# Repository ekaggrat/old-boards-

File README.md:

I collected an curated most of the common 3d printer controller boards made between 2011 and 2019. A lot of them have completely disappeared from the internet. This is just to have a library of the old board for reference.

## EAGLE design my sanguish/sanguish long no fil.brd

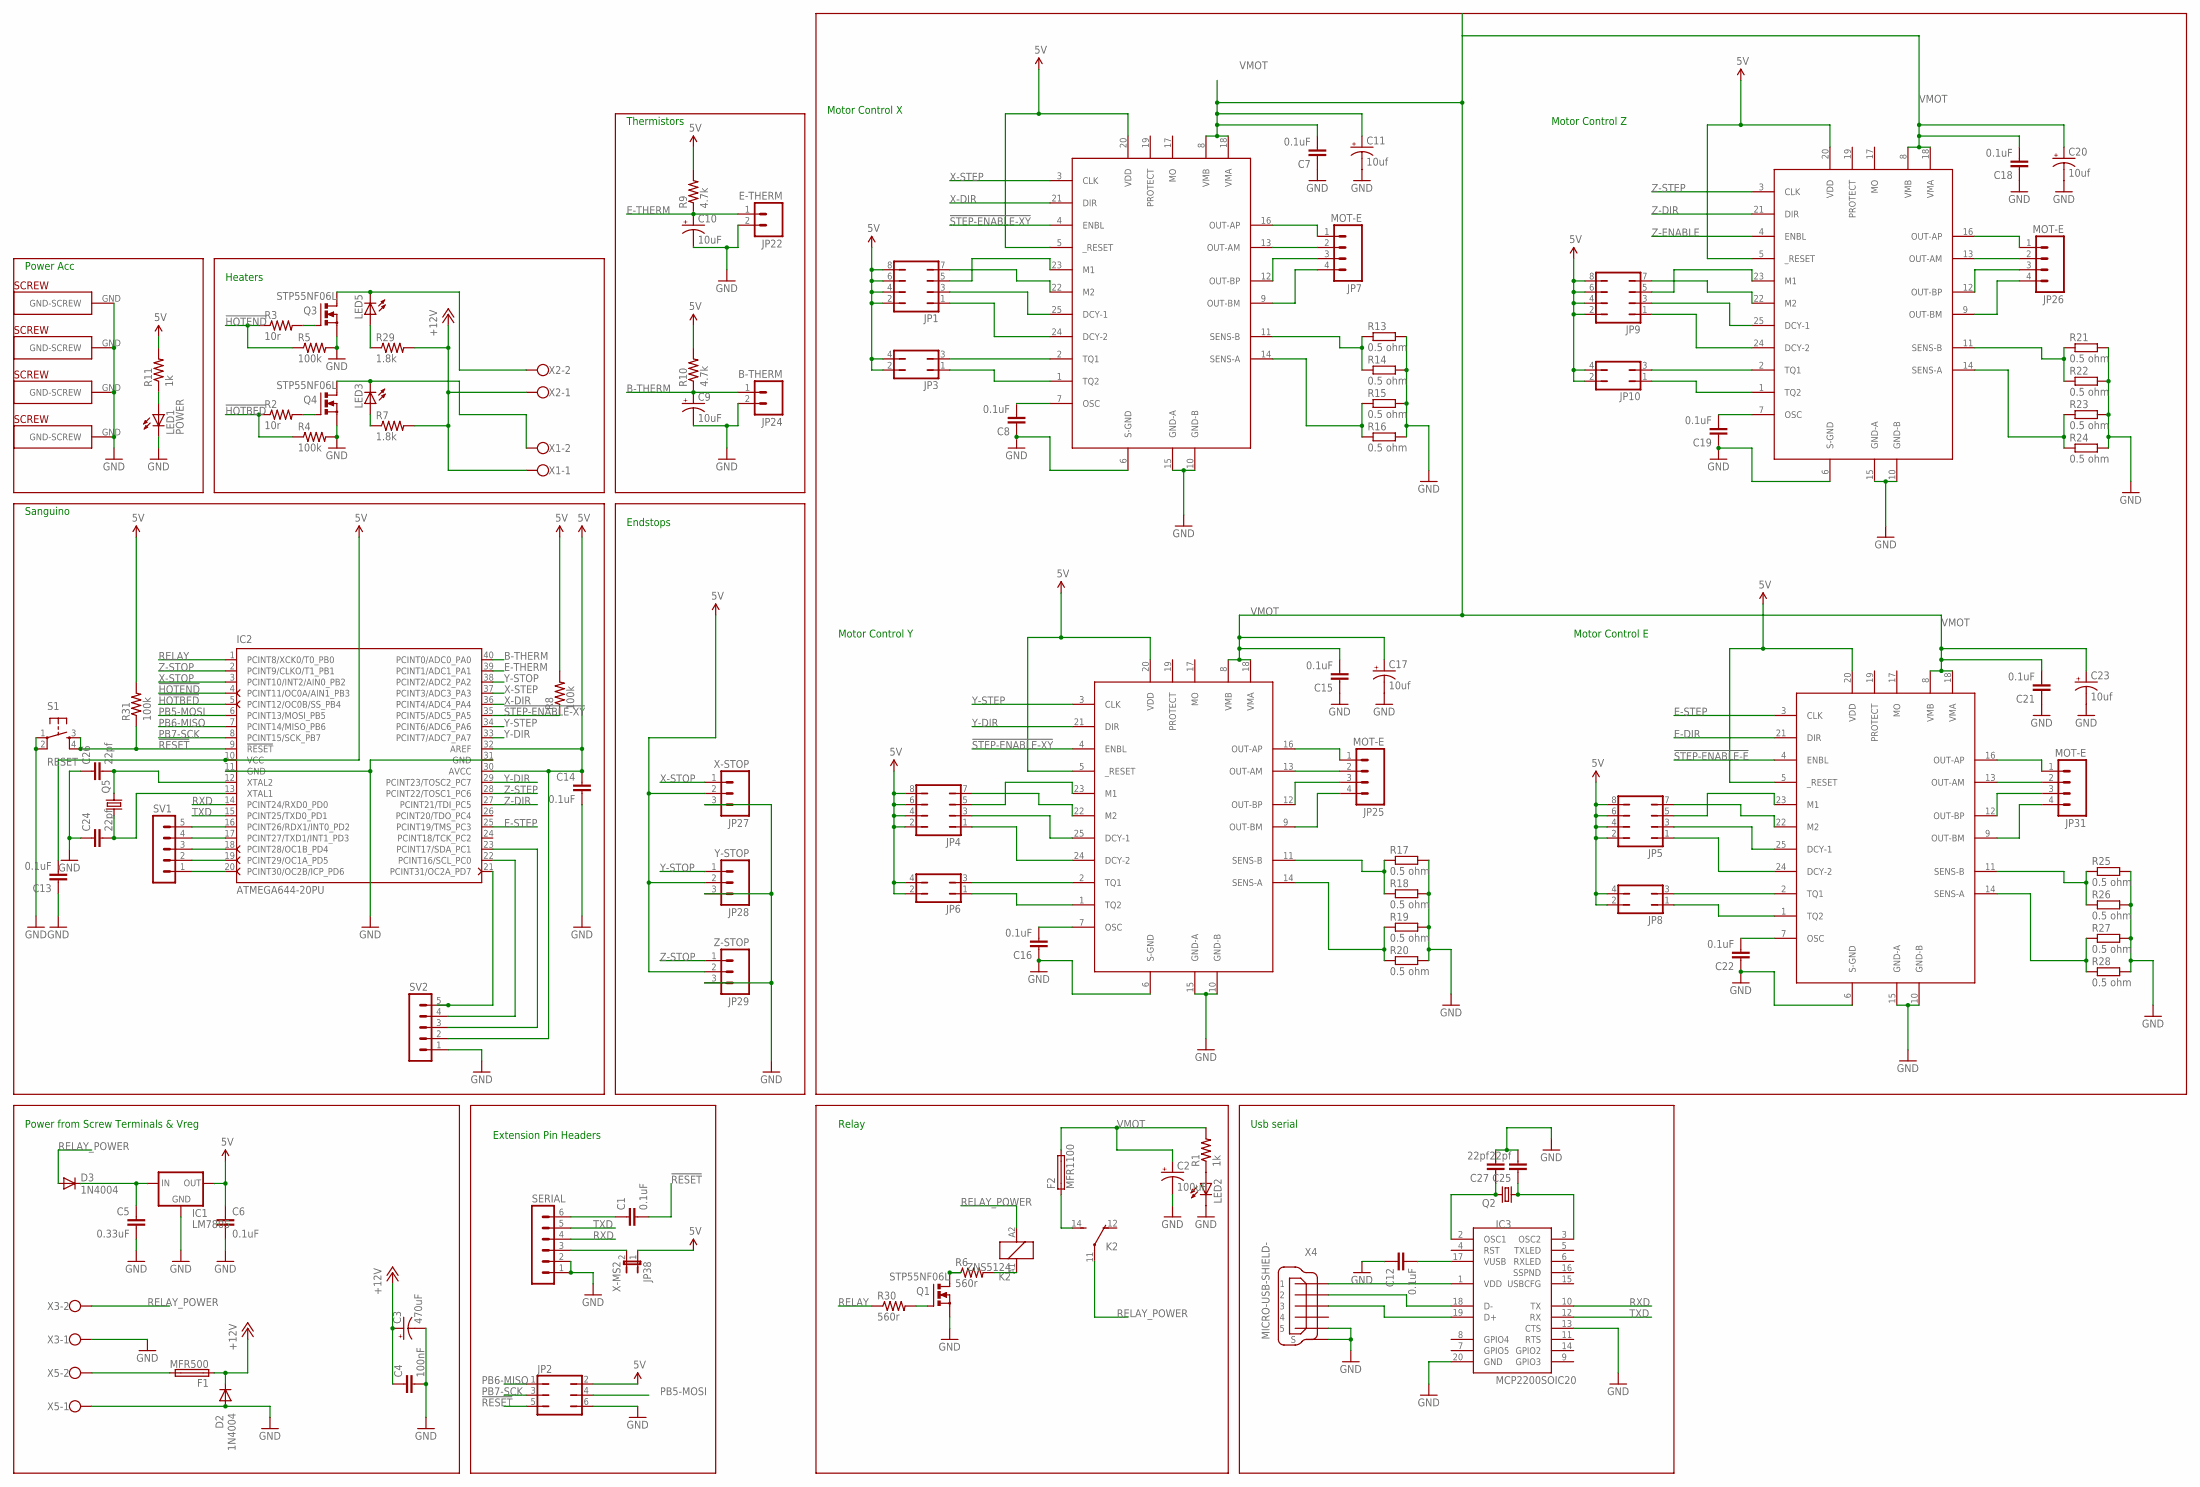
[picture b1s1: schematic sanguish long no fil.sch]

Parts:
C1, C6, C7, C8, C12, C13, C14, C15, C16, C18, C19, C21, C22: 0.1uF; CAP-PTH-SMALL2
C2: 100uF; CPOL-RADIAL-10UF-25V
C3: 470uF; E3,5-8
C4: 100nF; C2.5-3
C5: 0.33uF; CAP-PTH-SMALL2
C9, C10: 10uF; CPOL-RADIAL-10UF-25V
C11, C17, C20, C23: 10uf; CPOL-RADIAL-100UF-25V
C24, C25, C26, C27: 22pf; CAP-PTH-SMALL2
D2, D3: 1N4004; DO41-10
F1: MFR500
F2: MFR1100
IC1: LM7805; 78XXL-CUSTOM
IC2: ATMEGA644-20PU; DIL40
IC3: MCP2200SOIC20; SOIC20
JP1, JP4, JP5, JP9: JP4Q
JP2: JP3Q
JP3, JP6, JP8, JP10: JP2Q
JP7, JP25, JP26, JP31: MOT-E; MOLEX-1X4
JP22: E-THERM; 1X02
JP24: B-THERM; 1X02
JP27: X-STOP; MOLEX-1X3
JP28: Y-STOP; MOLEX-1X3
JP29: Z-STOP; MOLEX-1X3
JP38: X-MS2; 1X02
K2: ZNS5124; ZN5
LED1: POWER; LED3MM
LED2, LED3, LED5: LED3MM
Q1, Q3, Q4: STP55NF06L; TO220BV
Q2, Q5: CRYSTALHC49S; HC49/S
R1, R11: 1k; 0207/2V
R2, R3: 10r; 0207/2V
R4, R5, R8, R31: 100k; 0207/2V
R6, R30: 560r; 0207/2V
R7, R29: 1.8k; 0207/2V
R9, R10: 4.7k; 0207/2V
R13, R14, R15, R16, R17, R18, R19, R20, R21, R22, R23, R24, R25, R26, R27, R28: 0.5 ohm; 0207/10
S1: RESET; TACTILE-PTH
SERIAL: MA06-1
SV1, SV2: MA05-1
U$7, U$17, U$37, U$38: PLATED-SCREW; PLATEDSCREW
U$21, U$43, U$46: TB6560; ZIP25
X1, X3, X5: W237-102; MPN 237-102
X2: W237-102
X4: MICRO-USB-SHIELD-; 10118192-0001LF
XMOT: TB6560; ZIP25

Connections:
5V: C6.1, C13.2, C14.1, IC1.OUT, IC2.10 (VCC), IC2.30 (AVCC), IC2.32 (AREF), JP1.2, JP1.4, JP1.6, JP1.8, JP2.2, JP3.2, JP3.4, JP4.2, JP4.4, JP4.6, JP4.8, JP5.2, JP5.4, JP5.6, JP5.8, JP6.2, JP6.4, JP8.2, JP8.4, JP9.2, JP9.4, JP9.6, JP9.8, JP10.2, JP10.4, JP27.2, JP28.2, JP29.2, JP38.1, R8.2, R9.2, R10.2, R11.2, R31.2, SV2.2, U$21.5 (_RESET), U$21.20 (VDD), U$43.5 (_RESET), U$43.20 (VDD), U$46.5 (_RESET), U$46.20 (VDD), XMOT.5 (_RESET), XMOT.20 (VDD)
!HOTBED: IC2.5 (PCINT12/OC0B/SS_PB4), R2.1, R4.1
!HOTEND: IC2.4 (PCINT11/OC0A/AIN1_PB3), R3.1, R5.1
!RESET: C1.2, IC2.9 (!RESET), JP2.5, R31.1, S1.3, S1.4
!STEP-ENABLE-E: U$46.4 (ENBL)
!STEP-ENABLE-XY: IC2.35 (PCINT5/ADC5_PA5), R8.1, U$21.4 (ENBL), XMOT.4 (ENBL)
+12V: C3.+, C4.1, D2.C, F1.1, R7.2, R29.2, X1.1, X2.1
B-THERM: C9.1 (+), IC2.40 (PCINT0/ADC0_PA0), JP24.1, R10.1
E-DIR: U$46.21 (DIR)
E-STEP: IC2.25 (PCINT19/TMS_PC3), U$46.3 (CLK)
E-THERM: C10.1 (+), IC2.39 (PCINT1/ADC1_PA1), JP22.1, R9.1
GND: C2.2 (-), C3.-, C4.2, C5.2, C6.2, C7.1, C8.1, C9.2 (-), C10.2 (-), C11.2 (-), C12.1, C13.1, C14.2, C15.1, C16.1, C17.2 (-), C18.1, C19.1, C20.2 (-), C21.1, C22.1, C23.2 (-), C24.1, C25.2, C26.1, C27.2, D2.A, IC1.GND, IC2.11 (GND), IC2.31 (GND), IC3.13 (CTS), IC3.20 (GND), JP2.6, JP22.2, JP24.2, JP27.3, JP28.3, JP29.3, LED1.K (C), LED2.K (C), Q1.S, Q3.S, Q4.S, R4.2, R5.2, R13.2, R14.2, R15.2, R16.2, R17.2, R18.2, R19.2, R20.2, R21.2, R22.2, R23.2, R24.2, R25.2, R26.2, R27.2, R28.2, S1.1, S1.2, SERIAL.1, SERIAL.2, SV2.1, U$7.GND, U$17.GND, U$21.6 (S-GND), U$21.10 (GND-B), U$21.15 (GND-A), U$37.GND, U$38.GND, U$43.6 (S-GND), U$43.10 (GND-B), U$43.15 (GND-A), U$46.6 (S-GND), U$46.10 (GND-B), U$46.15 (GND-A), X3.1, X4.5, X4.M1 (S), X4.M2 (S), X4.M3 (S), X4.M4 (S), X4.M5 (S), X4.M6 (S), X5.1, XMOT.6 (S-GND), XMOT.10 (GND-B), XMOT.15 (GND-A)
LED1: LED1.A, R11.1
unnamed: JP7.1, XMOT.16 (OUT-AP)
unnamed: JP25.1, U$21.16 (OUT-AP)
unnamed: JP7.2, XMOT.13 (OUT-AM)
unnamed: JP7.3, XMOT.12 (OUT-BP)
unnamed: JP7.4, XMOT.9 (OUT-BM)
unnamed: JP5.7, U$46.22 (M2)
unnamed: JP1.7, XMOT.22 (M2)
unnamed: JP1.3, XMOT.25 (DCY-1)
unnamed: JP1.1, XMOT.24 (DCY-2)
unnamed: JP10.3, U$43.2 (TQ1)
unnamed: JP3.1, XMOT.1 (TQ2)
unnamed: JP5.5, U$46.23 (M1)
unnamed: JP25.2, U$21.13 (OUT-AM)
unnamed: JP25.3, U$21.12 (OUT-BP)
unnamed: R13.1, R14.1, XMOT.11 (SENS-B)
unnamed: R15.1, R16.1, XMOT.14 (SENS-A)
unnamed: JP25.4, U$21.9 (OUT-BM)
unnamed: JP9.7, U$43.22 (M2)
unnamed: C8.2, XMOT.7 (OSC)
unnamed: JP4.7, U$21.22 (M2)
unnamed: JP4.3, U$21.25 (DCY-1)
unnamed: JP4.1, U$21.24 (DCY-2)
unnamed: JP9.5, U$43.23 (M1)
unnamed: JP8.3, U$46.2 (TQ1)
unnamed: JP5.3, U$46.25 (DCY-1)
unnamed: R17.1, R18.1, U$21.11 (SENS-B)
unnamed: R19.1, R20.1, U$21.14 (SENS-A)
unnamed: C16.2, U$21.7 (OSC)
unnamed: JP26.1, U$43.16 (OUT-AP)
unnamed: JP26.2, U$43.13 (OUT-AM)
unnamed: JP26.3, U$43.12 (OUT-BP)
unnamed: JP26.4, U$43.9 (OUT-BM)
unnamed: JP5.1, U$46.24 (DCY-2)
unnamed: JP6.3, U$21.2 (TQ1)
unnamed: JP8.1, U$46.1 (TQ2)
unnamed: JP3.3, XMOT.2 (TQ1)
unnamed: JP4.5, U$21.23 (M1)
unnamed: JP1.5, XMOT.23 (M1)
unnamed: JP9.3, U$43.25 (DCY-1)
unnamed: R21.1, R22.1, U$43.11 (SENS-B)
unnamed: R23.1, R24.1, U$43.14 (SENS-A)
unnamed: C19.2, U$43.7 (OSC)
unnamed: JP31.1, U$46.16 (OUT-AP)
unnamed: JP31.2, U$46.13 (OUT-AM)
unnamed: JP31.3, U$46.12 (OUT-BP)
unnamed: JP31.4, U$46.9 (OUT-BM)
unnamed: LED2.A, R1.1
unnamed: IC2.16 (PCINT26/RDX1/INT0_PD2), SV1.5
unnamed: IC2.17 (PCINT27/TXD1/INT1_PD3), SV1.4
unnamed: IC2.18 (PCINT28/OC1B_PD4), SV1.3
unnamed: IC2.19 (PCINT29/OC1A_PD5), SV1.2
unnamed: R25.1, R26.1, U$46.11 (SENS-B)
unnamed: R27.1, R28.1, U$46.14 (SENS-A)
unnamed: C22.2, U$46.7 (OSC)
unnamed: LED3.K (C), Q4.D, X1.2
unnamed: IC2.20 (PCINT30/OC2B/ICP_PD6), SV1.1
unnamed: LED5.K (C), Q3.D, X2.2
unnamed: Q4.G, R2.2
unnamed: Q3.G, R3.2
unnamed: IC2.21 (PCINT31/OC2A_PD7), SV2.5
unnamed: IC2.22 (PCINT16/SCL_PC0), SV2.4
unnamed: LED3.A, R7.1
unnamed: LED5.A, R29.1
unnamed: Q1.D, R6.1
unnamed: Q1.G, R30.2
unnamed: C5.1, D3.C, IC1.IN
unnamed: IC2.23 (PCINT17/SDA_PC1), SV2.3
unnamed: C1.1, SERIAL.6
unnamed: JP38.2, SERIAL.3
unnamed: F2.1, K2.14 (S)
unnamed: K2.A1 (1), R6.2
unnamed: F1.2, X5.2
unnamed: C12.2, IC3.17 (VUSB)
unnamed: JP6.1, U$21.1 (TQ2)
unnamed: IC3.1 (VDD), X4.1
unnamed: IC3.18 (D-), X4.2
unnamed: IC3.19 (D+), X4.3
unnamed: C26.2, IC2.12 (XTAL2), Q5.2
unnamed: C24.2, IC2.13 (XTAL1), Q5.1
unnamed: C27.1, IC3.2 (OSC1), Q2.2
unnamed: C25.1, IC3.3 (OSC2), Q2.1
PB5-MOSI: IC2.6 (PCINT13/MOSI_PB5), JP2.4
PB6-MISO: IC2.7 (PCINT14/MISO_PB6), JP2.1
PB7-SCK: IC2.8 (PCINT15/SCK_PB7), JP2.3
RELAY: IC2.1 (PCINT8/XCK0/T0_PB0), R30.1
RELAY_POWER: D3.A, K2.11, K2.A2 (2), X3.2
RXD: IC2.14 (PCINT24/RXD0_PD0), IC3.10 (TX), SERIAL.4
TXD: IC2.15 (PCINT25/TXD0_PD1), IC3.12 (RX), SERIAL.5
VMOT: C2.1 (+), C7.2, C11.1 (+), C15.2, C17.1 (+), C18.2, C20.1 (+), C21.2, C23.1 (+), F2.2, R1.2, U$21.8 (VMB), U$21.18 (VMA), U$43.8 (VMB), U$43.18 (VMA), U$46.8 (VMB), U$46.18 (VMA), XMOT.8 (VMB), XMOT.18 (VMA)
X-DIR: IC2.36 (PCINT4/ADC4_PA4), XMOT.21 (DIR)
X-STEP: IC2.37 (PCINT3/ADC3_PA3), XMOT.3 (CLK)
X-STOP: IC2.3 (PCINT10/INT2/AIN0_PB2), JP27.1
Y-DIR: IC2.29 (PCINT23/TOSC2_PC7), IC2.33 (PCINT7/ADC7_PA7), U$21.21 (DIR)
Y-STEP: IC2.34 (PCINT6/ADC6_PA6), U$21.3 (CLK)
Y-STOP: IC2.38 (PCINT2/ADC2_PA2), JP28.1
Z-DIR: IC2.27 (PCINT21/TDI_PC5), U$43.21 (DIR)
Z-ENABLE: U$43.4 (ENBL)
Z-STEP: IC2.28 (PCINT22/TOSC1_PC6), U$43.3 (CLK)
Z-STOP: IC2.2 (PCINT9/CLKO/T1_PB1), JP29.1

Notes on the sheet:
Motor Control X
Motor Control Y
Motor Control Z
Motor Control E
Thermistors
Endstops
Sanguino
Power Acc
Extension Pin Headers
Power from Screw Terminals & Vreg
Usb serial
Relay
Heaters

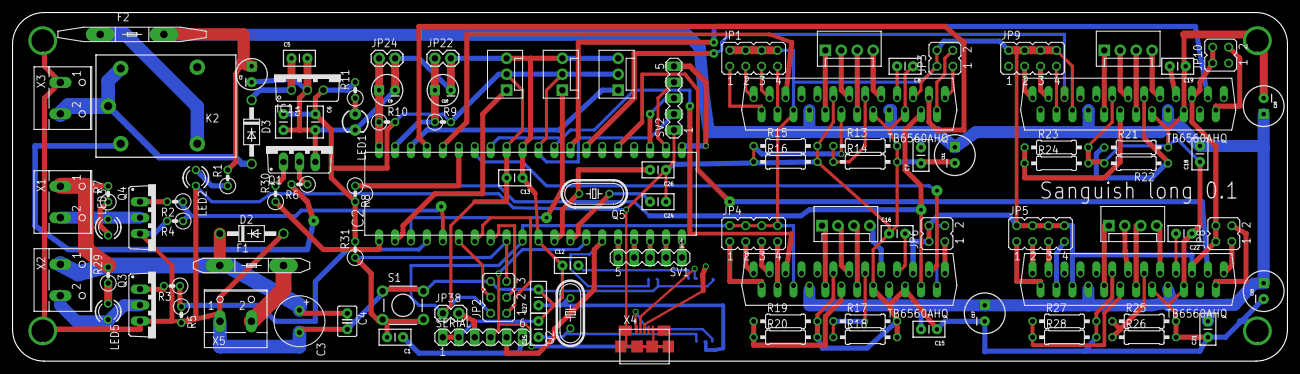
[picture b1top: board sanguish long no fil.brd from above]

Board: 2 copper layers, 203.2 x 55.5 mm, 110 parts (1 on the bottom side), 109 nets.

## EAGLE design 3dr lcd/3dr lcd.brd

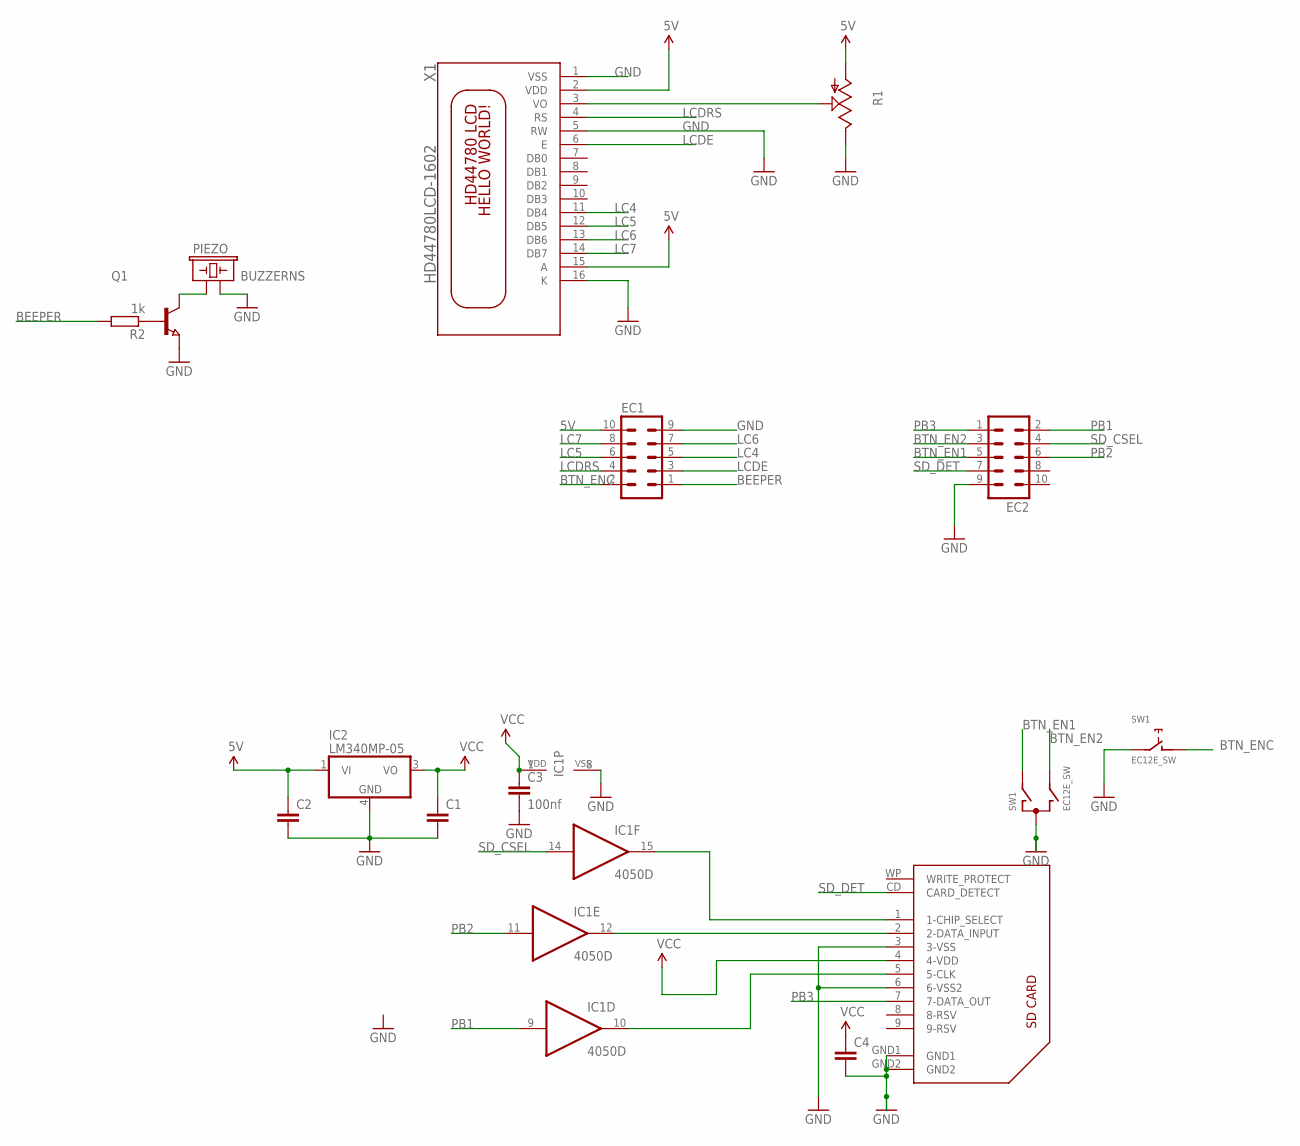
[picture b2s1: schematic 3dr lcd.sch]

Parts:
C1, C2, C4: C-EUC1206K; C1206K
C3: 100nf; C1206K
EC1, EC2: ML10
IC1: 4050D; SO16
IC2: LM340MP-05; SOT223
PIEZO: BUZZERNS; BUZZER-12MM-NS
Q1: NPN-TRANSISTOR_SOT23; SOT23
R1: TRIM_US-3364W; 3364W
R2: 1k; R0805
SW1: EC12E_SW; ALPS_EC12E_SW
U$2: SDCARD; 3M-SDCARD
X1: HD44780LCD-1602; LCD1602

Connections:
5V: EC1.10, R1.1 (A), X1.2 (VDD), X1.15 (A)
BEEPER: EC1.1, R2.2
BTN_EN1: EC2.5, SW1.A
BTN_EN2: EC2.3, SW1.B
BTN_ENC: EC1.2, SW1.D (1)
D31: PIEZO.+ (1), Q1.3 (C)
GND: C1.2, C2.2, C3.2, C4.2, EC1.9, EC2.9, IC1.8 (VSS), IC2.4 (GND), PIEZO.- (2), Q1.2 (E), R1.3 (E), SW1.C, SW1.E (2), U$2.3 (3-VSS), U$2.6 (6-VSS2), U$2.GND1, U$2.GND2, X1.1 (VSS), X1.5 (RW), X1.16 (K)
LC4: EC1.5, X1.11 (DB4)
LC5: EC1.6, X1.12 (DB5)
LC6: EC1.7, X1.13 (DB6)
LC7: EC1.8, X1.14 (DB7)
LCDE: EC1.3, X1.6 (E)
LCDRS: EC1.4, X1.4 (RS)
unnamed: Q1.1 (B), R2.1
unnamed: R1.2 (S), X1.3 (VO)
unnamed: C2.1, IC2.1 (VI)
unnamed: IC1.15 (O), U$2.1 (1-CHIP_SELECT)
unnamed: IC1.12 (O), U$2.2 (2-DATA_INPUT)
unnamed: IC1.10 (O), U$2.5 (5-CLK)
PB1: EC2.2, IC1.9 (I)
PB2: EC2.6, IC1.11 (I)
PB3: EC2.1, U$2.7 (7-DATA_OUT)
SD_CSEL: EC2.4, IC1.14 (I)
SD_DET: EC2.7, U$2.CD (CARD_DETECT)
VCC: C1.1, C3.1, C4.1, IC1.1 (VDD), IC2.3 (VO), U$2.4 (4-VDD)

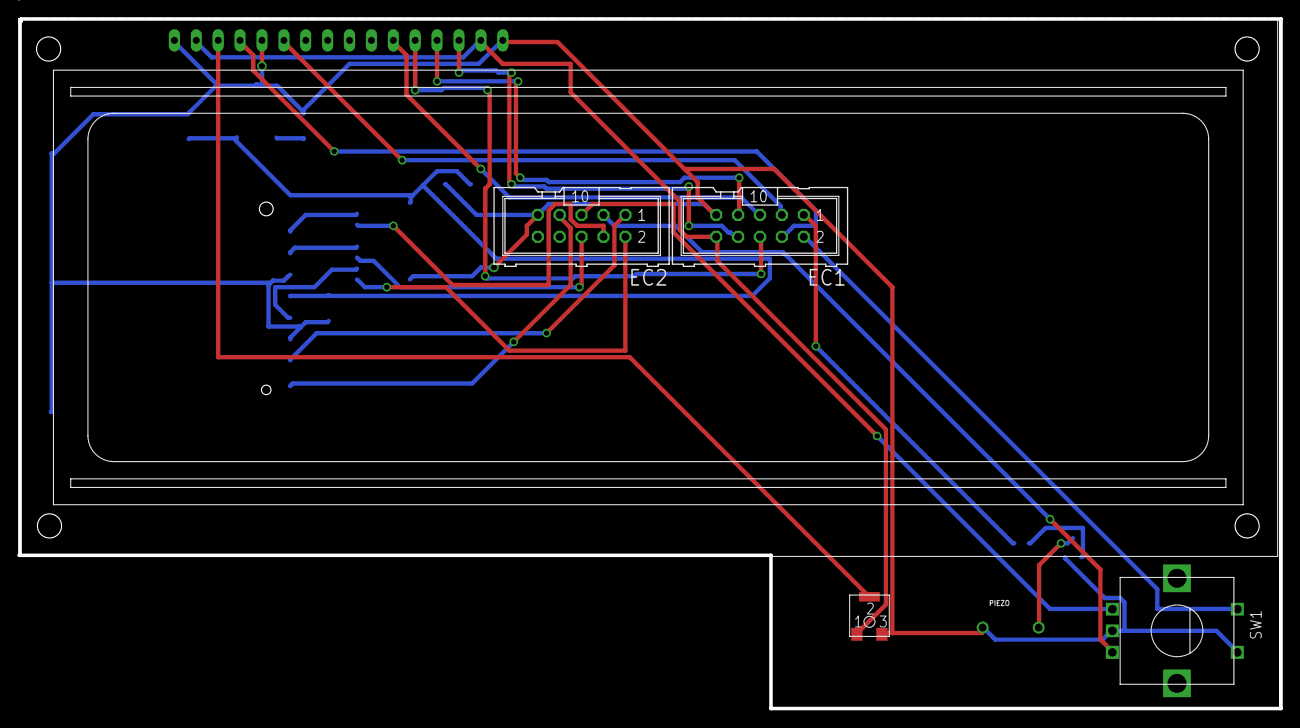
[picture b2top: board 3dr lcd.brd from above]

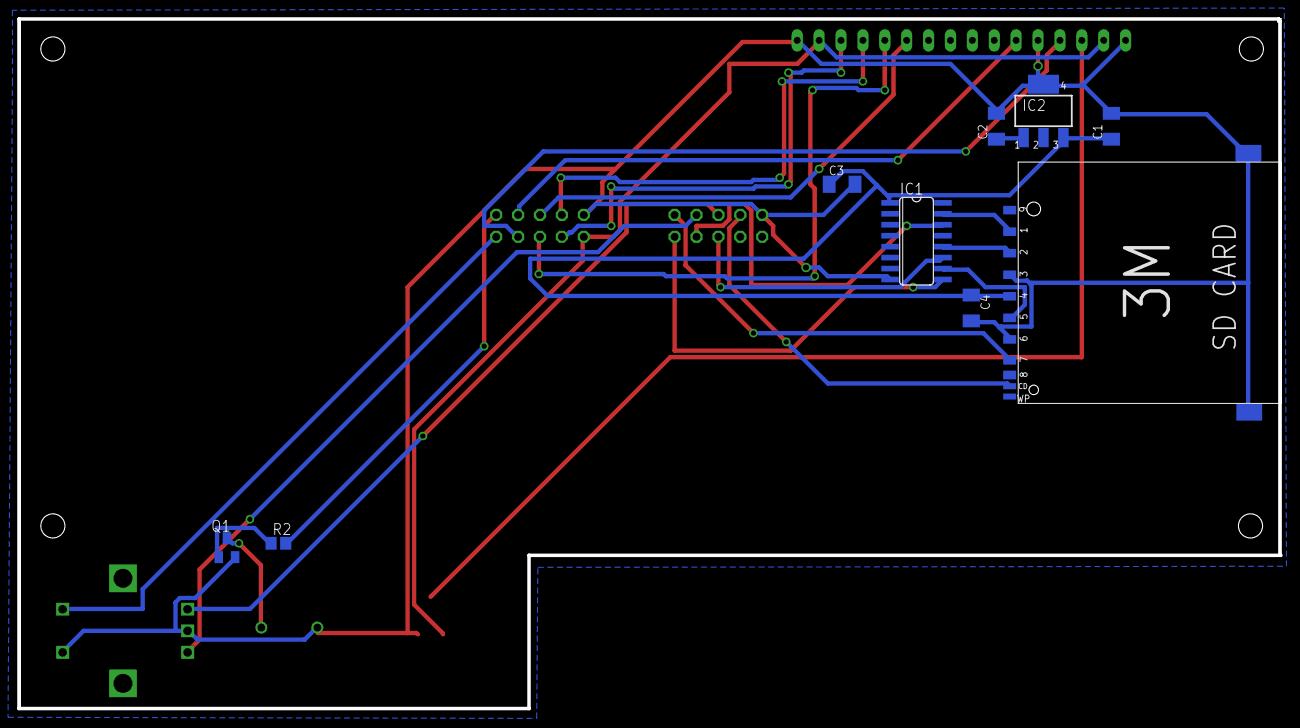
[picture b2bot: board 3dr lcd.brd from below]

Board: 2 copper layers, 146.3 x 80.0 mm, 15 parts (9 on the bottom side), 25 nets.

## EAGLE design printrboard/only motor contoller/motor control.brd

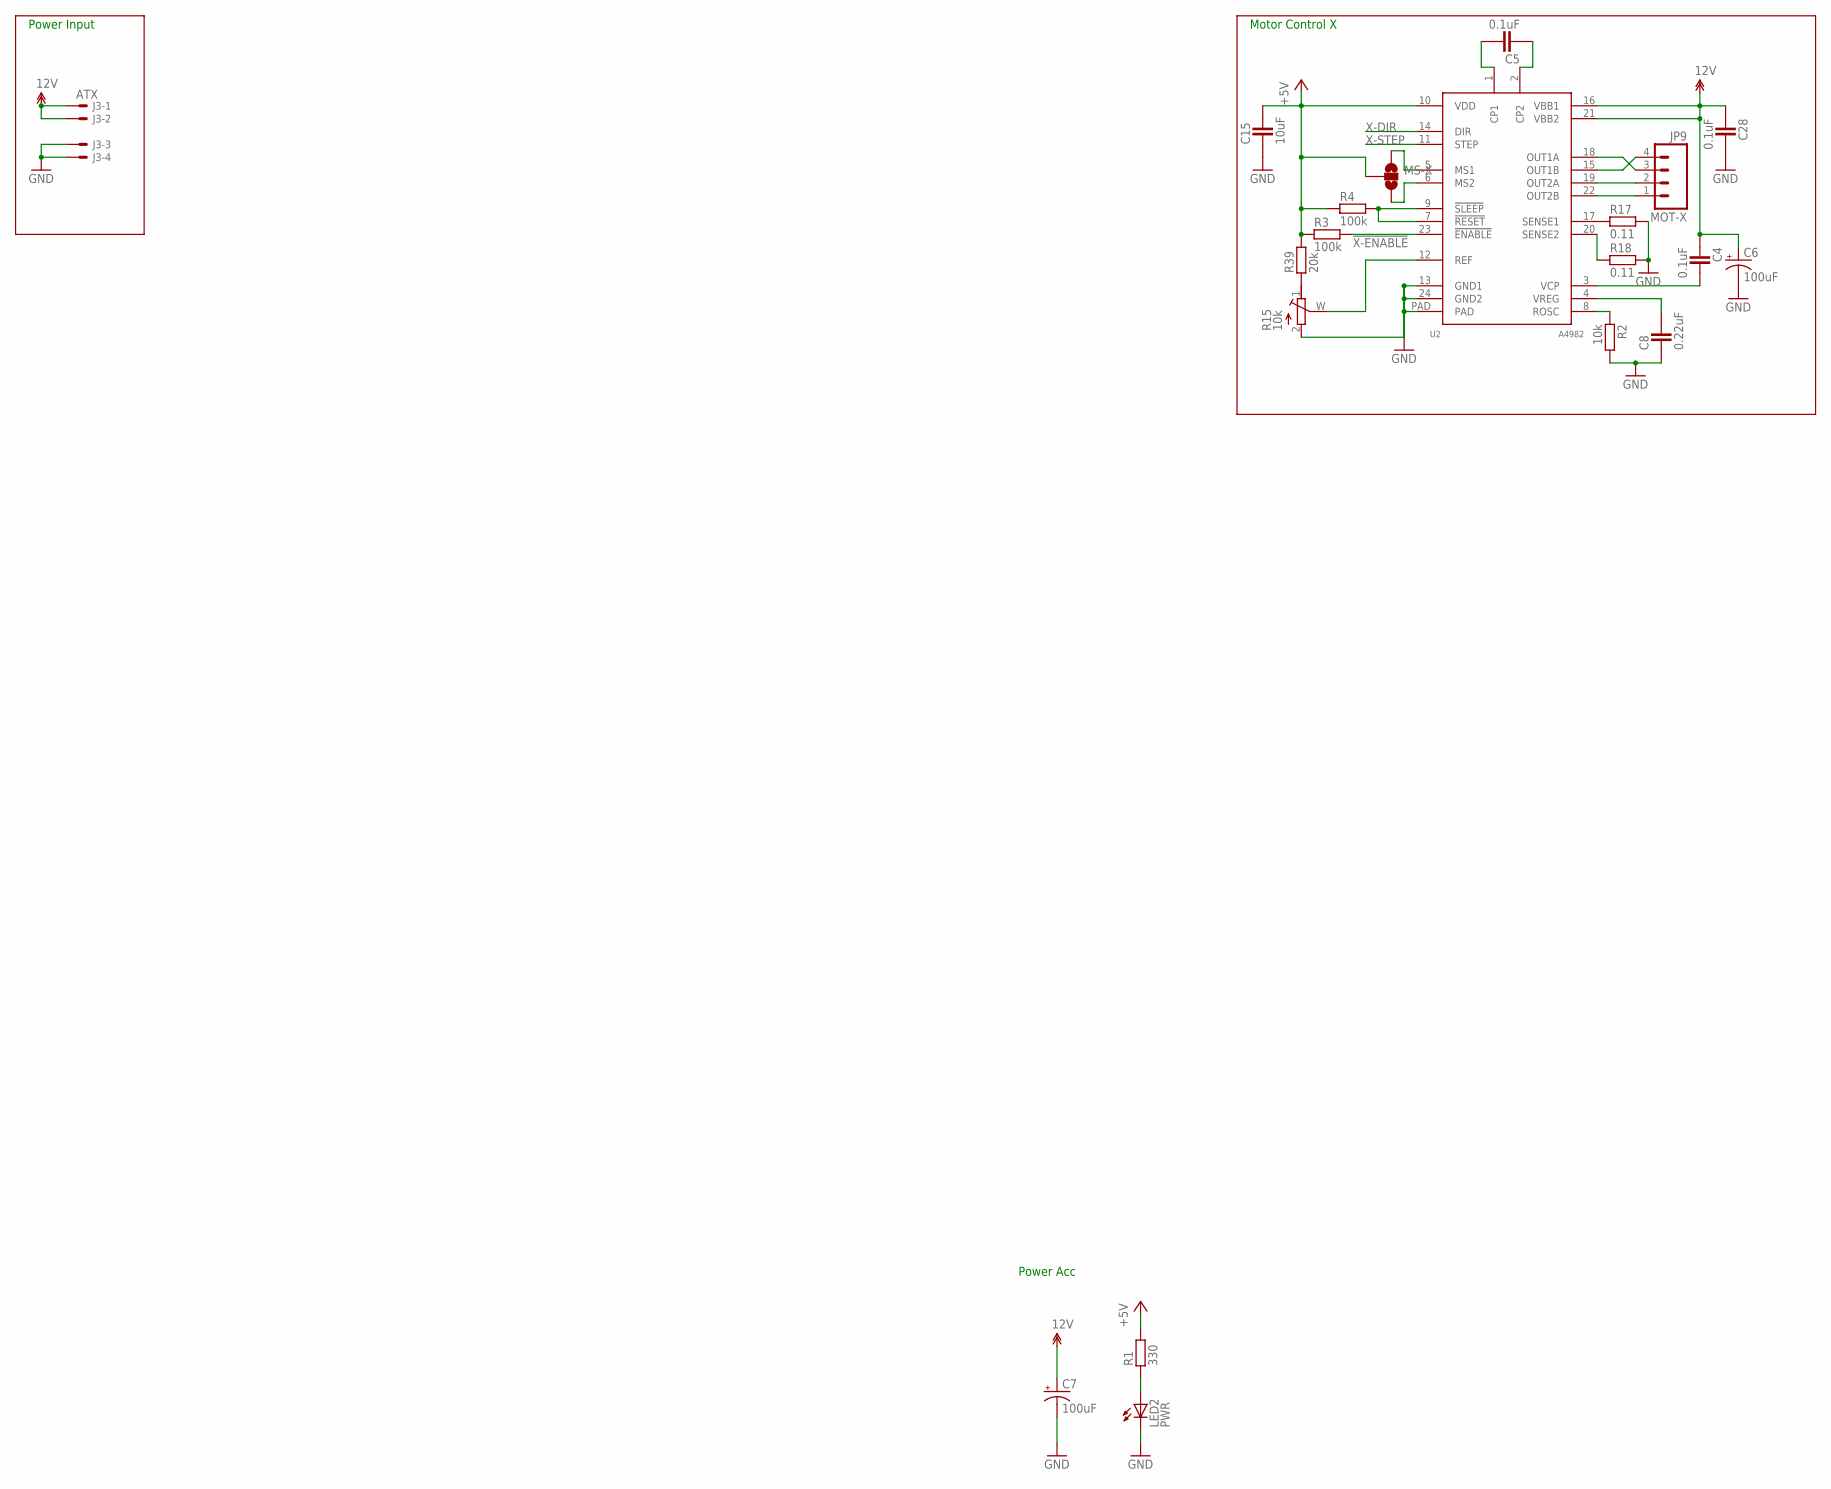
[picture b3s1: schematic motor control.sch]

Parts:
C4, C5, C28: 0.1uF; CAPC2012X145AN
C6, C7: 100uF; PANASONIC_D
C8: 0.22uF; CAPC2012X145AN
C15: 10uF; CAPC2012X145AN
J3: ATX; 5566-4
JP9: MOT-X; MOLEX-1X4
LED2: PWR; CHIP-LED0805
MS-X: SOLDERJUMPER_2WAYCONNECTED; SJ_3_CONNECTED
R1: 330; RESC2012X70N
R2: 10k; RESC2012X70N
R3, R4: 100k; RESC2012X70N
R15: 10k; RTRIM-ST4ETB
R17, R18: 0.11; RESC2012X70N
R39: 20k; RESC2012X70N
U2: A4982; TSSOP-24

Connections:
12V: C4.1, C6.+, C7.+, C28.1, J3.1, J3.2, U2.16 (VBB1), U2.21 (VBB2)
!X-ENABLE: R3.2, U2.23 (!ENABLE)
+5V: C15.2, MS-X.2, R1.2, R3.1, R4.1, R39.2, U2.10 (VDD)
GND: C6.-, C7.-, C8.1, C15.1, C28.2, J3.3, J3.4, LED2.C, R2.2, R15.2 (E), R17.2, R18.2, U2.13 (GND1), U2.24 (GND2), U2.PAD
unnamed: LED2.A, R1.1
unnamed: JP9.3, U2.18 (OUT1A)
unnamed: C5.2, U2.1 (CP1)
unnamed: C5.1, U2.2 (CP2)
unnamed: R2.1, U2.8 (ROSC)
unnamed: R17.1, U2.17 (SENSE1)
unnamed: R18.1, U2.20 (SENSE2)
unnamed: C4.2, U2.3 (VCP)
unnamed: JP9.4, U2.15 (OUT1B)
unnamed: R15.W (S), U2.12 (REF)
unnamed: C8.2, U2.4 (VREG)
unnamed: JP9.2, U2.19 (OUT2A)
unnamed: R4.2, U2.7 (!RESET), U2.9 (!SLEEP)
unnamed: JP9.1, U2.22 (OUT2B)
unnamed: MS-X.1, U2.5 (MS1)
unnamed: MS-X.3, U2.6 (MS2)
unnamed: R15.1 (A), R39.1
X-DIR: U2.14 (DIR)
X-STEP: U2.11 (STEP)

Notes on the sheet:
Motor Control X
Power Acc
Power Input

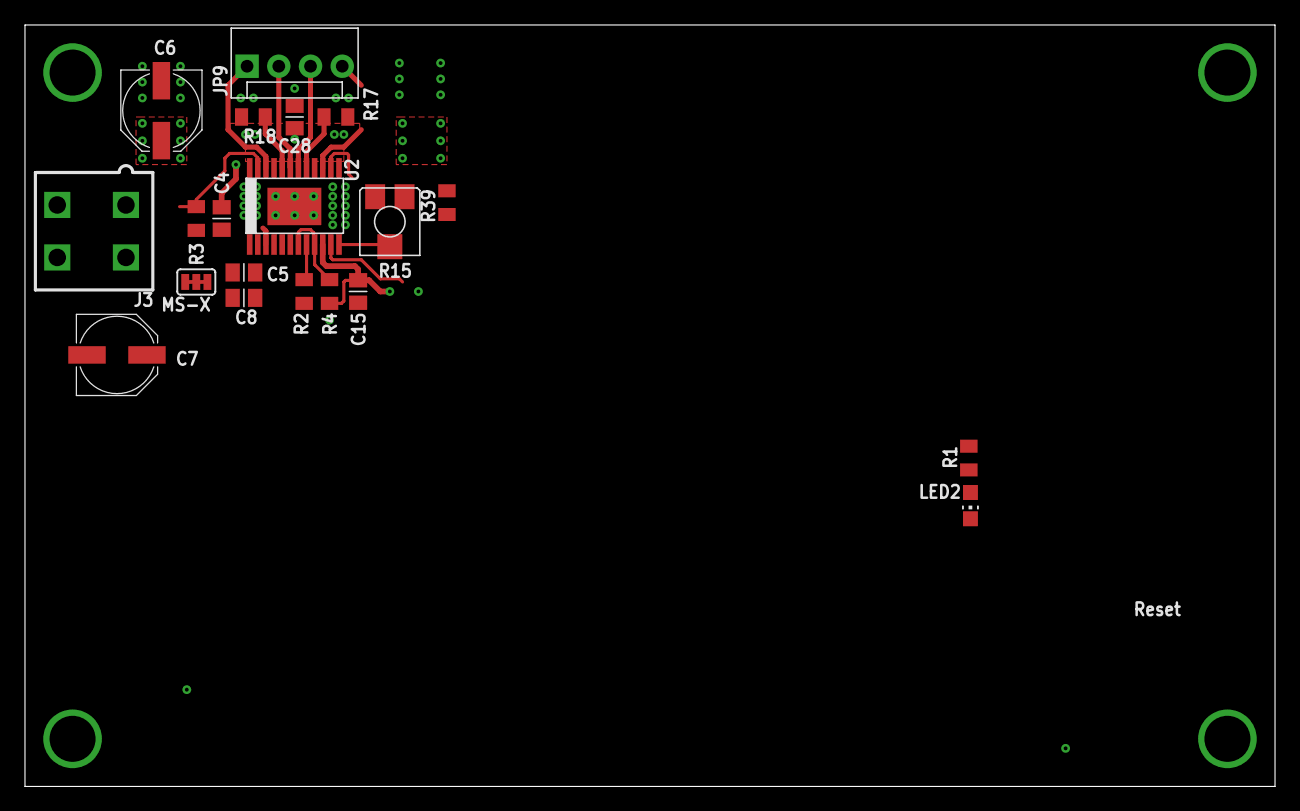
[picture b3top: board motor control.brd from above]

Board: 4 copper layers, 100.1 x 61.0 mm, 20 parts (0 on the bottom side), 21 nets.

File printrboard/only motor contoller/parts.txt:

Partlist

Exported from motor control.sch at 23/7/2012 PM 4:29:23

EAGLE Version 6.0.0 Copyright (c) 1988-2011 CadSoft

Assembly variant: 

Part     Value          Device                     Package        Library            Sheet

C4       0.1uF          CAPACITOR_0805             CAPC2012X145AN ipc-7351-capacitor 1
C5       0.1uF          CAPACITOR_0805             CAPC2012X145AN ipc-7351-capacitor 1
C6       100uF          CPOL-USD                   PANASONIC_D    rcl                1
C7       100uF          CPOL-USD                   PANASONIC_D    rcl                1
C8       0.22uF         CAPACITOR_0805             CAPC2012X145AN ipc-7351-capacitor 1
C15      10uF           CAPACITOR_0805             CAPC2012X145AN ipc-7351-capacitor 1
C28      0.1uF          CAPACITOR_0805             CAPC2012X145AN ipc-7351-capacitor 1
J3       ATX            5566-4                     5566-4         printrbot          1
JP9      MOT-X          M04POLAR                   MOLEX-1X4      SparkFun           1
LED2     PWR            LEDCHIP-LED0805            CHIP-LED0805   led                1
MS-X                    SOLDERJUMPER_2WAYCONNECTED SJ_3_CONNECTED printrbot          1
R1       330            RESISTOR_0805              RESC2012X70N   ipc-7351-resistor  1
R2       10k            RESISTOR_0805              RESC2012X70N   ipc-7351-resistor  1
R3       100k           RESISTOR_0805              RESC2012X70N   ipc-7351-resistor  1
R4       100k           RESISTOR_0805              RESC2012X70N   ipc-7351-resistor  1
R15      10k            RTRIM-ST-4EA               RTRIM-ST4ETB   printrbot          1
R17      0.11           RESISTOR_0805              RESC2012X70N   ipc-7351-resistor  1
R18      0.11           RESISTOR_0805              RESC2012X70N   ipc-7351-resistor  1
R39      20k            RESISTOR_0805              RESC2012X70N   ipc-7351-resistor  1
U2       A4982          A4982                      TSSOP-24       printrbot          1

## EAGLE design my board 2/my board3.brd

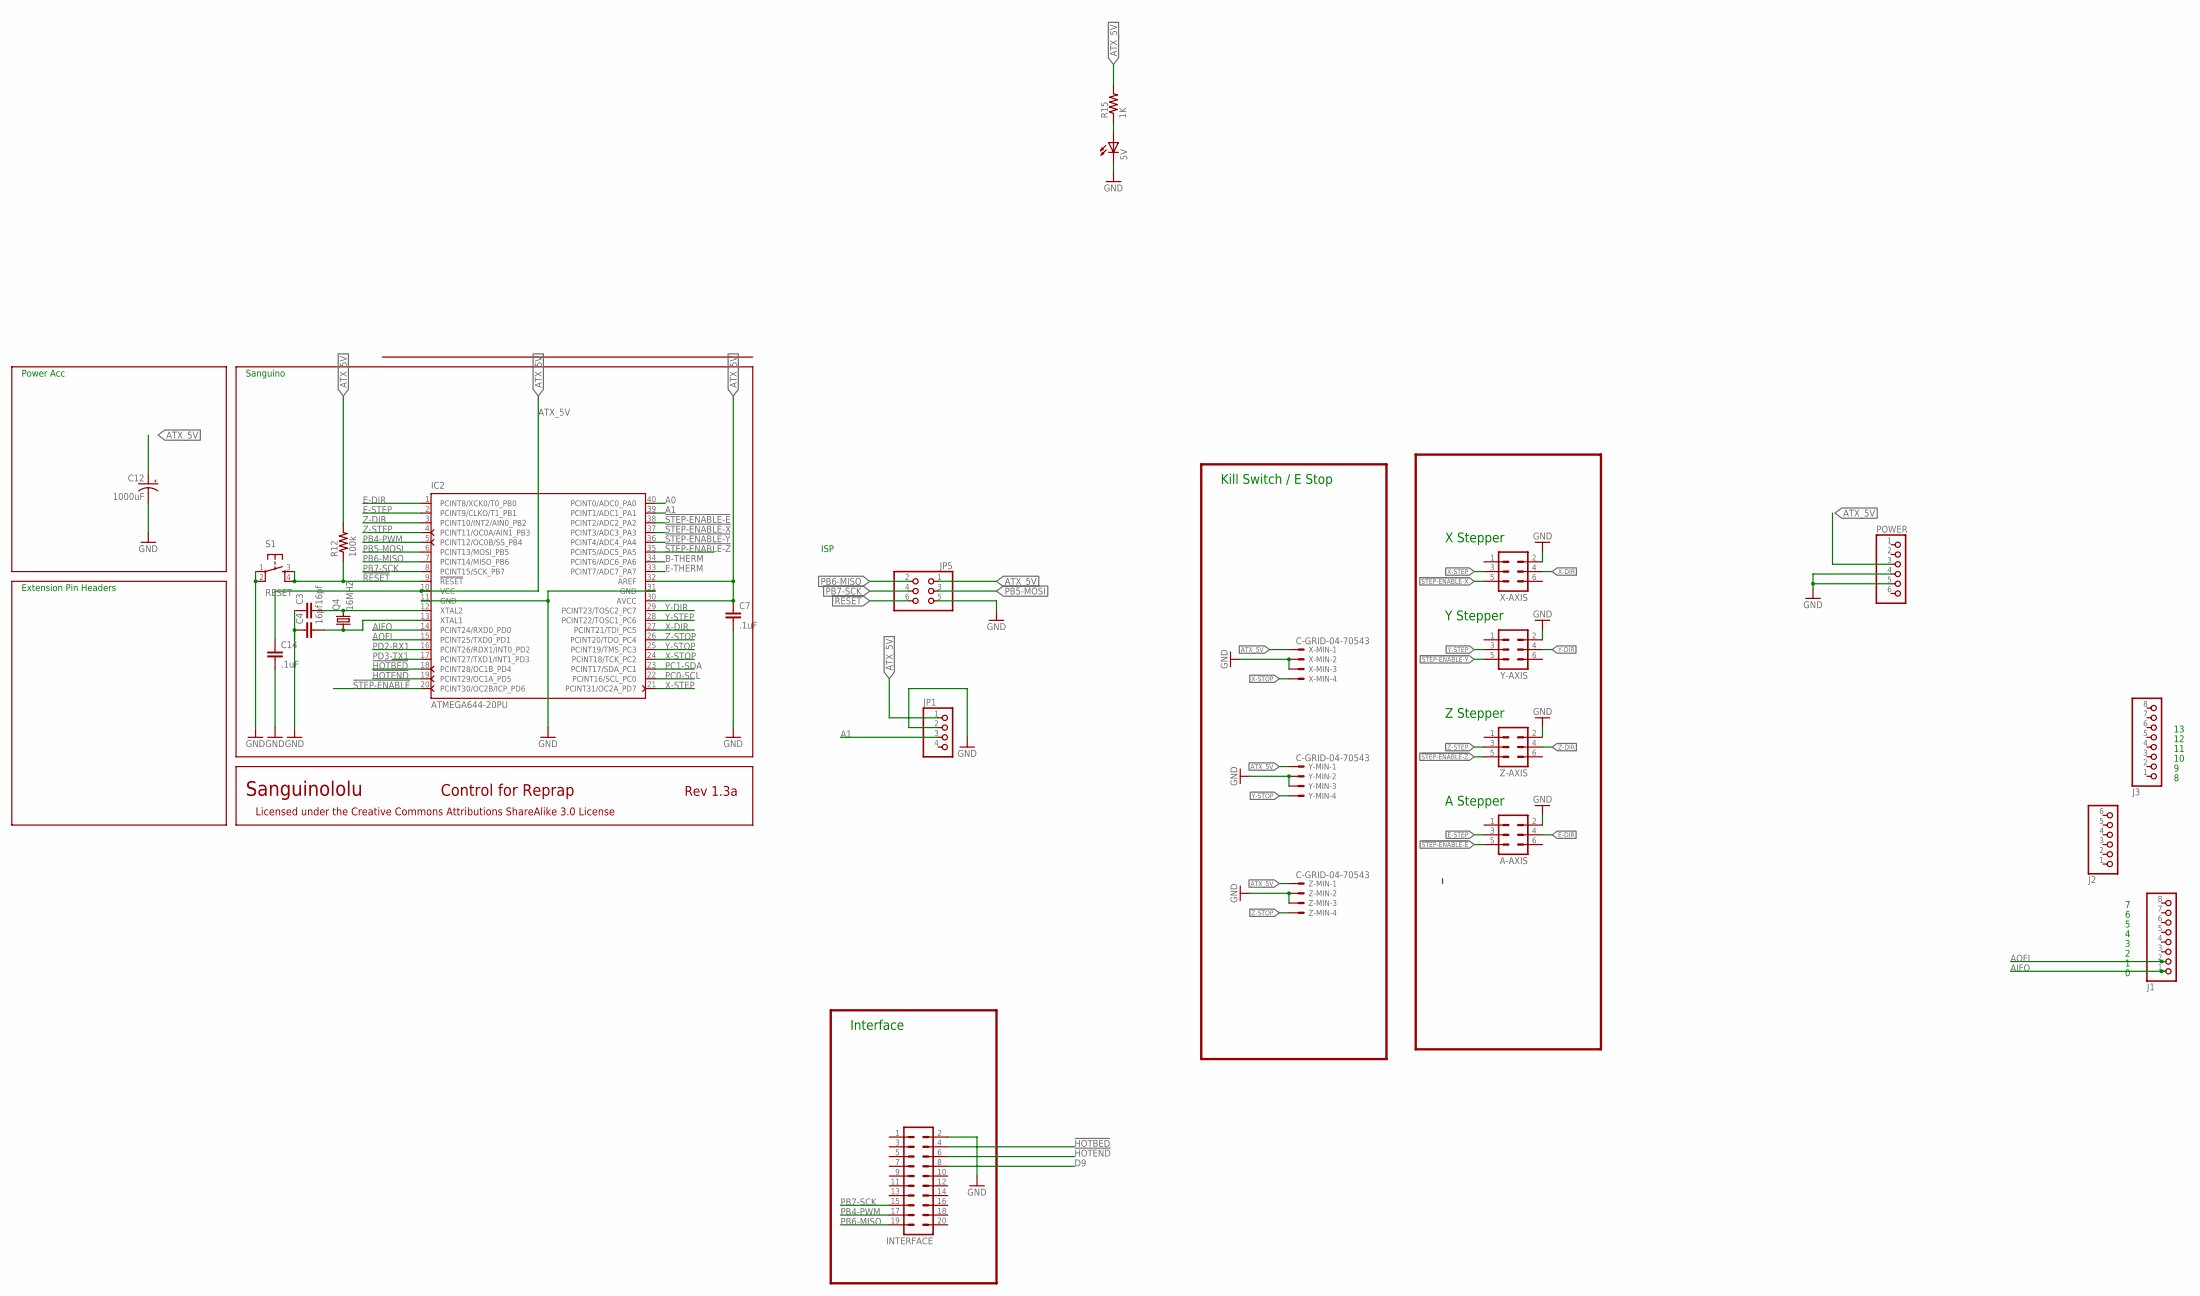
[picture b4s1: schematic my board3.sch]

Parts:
5V: LED0805; LED-0805
A-AXIS: ML6
C3, C4: 16pf; 0805
C7, C14: .1uF; 0805
C12: 1000uF; CPOL-RADIAL-1000UF-25V
IC2: ATMEGA644-20PU; DIL40
INTERFACE: ML20
J1, J3: PINHD-1X8; 1X08
J2: PINHD-1X6; 1X06
JP1: PINHD-1X4; 1X04
JP5: PINHD-2X3; 2X03
POWER: PINHD-1X6; 1X06
Q4: 16MHZ; HC49/S
R12: 100k; AXIAL-0.3
R15: 1K; 0805
S1: RESET; TACTILE-PTH
X-AXIS: ML6
X-MIN: C-GRID-04-70543; 70543-04
Y-AXIS: ML6
Y-MIN: C-GRID-04-70543; 70543-04
Z-AXIS: ML6
Z-MIN: C-GRID-04-70543; 70543-04

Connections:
!HOTBED: IC2.18 (PCINT28/OC1B_PD4), INTERFACE.4
!HOTEND: IC2.19 (PCINT29/OC1A_PD5), INTERFACE.6
!RESET: IC2.9 (!RESET), JP5.6, R12.P$1 (1), S1.3, S1.4
!STEP-ENABLE: IC2.20 (PCINT30/OC2B/ICP_PD6)
!STEP-ENABLE-E: A-AXIS.5, IC2.38 (PCINT2/ADC2_PA2)
!STEP-ENABLE-X: IC2.37 (PCINT3/ADC3_PA3), X-AXIS.5
!STEP-ENABLE-Y: IC2.36 (PCINT4/ADC4_PA4), Y-AXIS.5
!STEP-ENABLE-Z: IC2.35 (PCINT5/ADC5_PA5), Z-AXIS.5
A0: IC2.40 (PCINT0/ADC0_PA0)
A1: IC2.39 (PCINT1/ADC1_PA1), JP1.3
AIFO: IC2.14 (PCINT24/RXD0_PD0), J1.1
AOFI: IC2.15 (PCINT25/TXD0_PD1), J1.2
ATX_5V: C7.1, C12.1 (+), C14.1, IC2.10 (VCC), IC2.30 (AVCC), IC2.32 (AREF), JP1.1, JP5.1, POWER.3, R12.P$2 (2), R15.2, X-MIN.1, Y-MIN.1, Z-MIN.1
B-THERM: IC2.34 (PCINT6/ADC6_PA6)
D9: INTERFACE.8
E-DIR: A-AXIS.4, IC2.1 (PCINT8/XCK0/T0_PB0)
E-STEP: A-AXIS.3, IC2.2 (PCINT9/CLKO/T1_PB1)
E-THERM: IC2.33 (PCINT7/ADC7_PA7)
GND: 5V.C, A-AXIS.2, C3.1, C4.1, C7.2, C12.2 (-), C14.2, IC2.11 (GND), IC2.31 (GND), INTERFACE.2, JP1.2, JP5.5, POWER.4, POWER.5, S1.1, S1.2, X-AXIS.2, X-MIN.2, X-MIN.3, Y-AXIS.2, Y-MIN.2, Y-MIN.3, Z-AXIS.2, Z-MIN.2, Z-MIN.3
unnamed: 5V.A, R15.1
unnamed: C3.2, IC2.12 (XTAL2), Q4.2
unnamed: C4.2, IC2.13 (XTAL1), Q4.1
PB4-PWM: IC2.5 (PCINT12/OC0B/SS_PB4), INTERFACE.17
PB5-MOSI: IC2.6 (PCINT13/MOSI_PB5), JP5.3
PB6-MISO: IC2.7 (PCINT14/MISO_PB6), INTERFACE.19, JP5.2
PB7-SCK: IC2.8 (PCINT15/SCK_PB7), INTERFACE.15, JP5.4
PC0-SCL: IC2.22 (PCINT16/SCL_PC0)
PC1-SDA: IC2.23 (PCINT17/SDA_PC1)
PD2-RX1: IC2.16 (PCINT26/RDX1/INT0_PD2)
PD3-TX1: IC2.17 (PCINT27/TXD1/INT1_PD3)
X-DIR: IC2.27 (PCINT21/TDI_PC5), X-AXIS.4
X-STEP: IC2.21 (PCINT31/OC2A_PD7), X-AXIS.3
X-STOP: IC2.24 (PCINT18/TCK_PC2), X-MIN.4
Y-DIR: IC2.29 (PCINT23/TOSC2_PC7), Y-AXIS.4
Y-STEP: IC2.28 (PCINT22/TOSC1_PC6), Y-AXIS.3
Y-STOP: IC2.25 (PCINT19/TMS_PC3), Y-MIN.4
Z-DIR: IC2.3 (PCINT10/INT2/AIN0_PB2), Z-AXIS.4
Z-STEP: IC2.4 (PCINT11/OC0A/AIN1_PB3), Z-AXIS.3
Z-STOP: IC2.26 (PCINT20/TDO_PC4), Z-MIN.4

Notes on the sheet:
ISP
Sanguino
Power Acc
Sanguinololu
Rev 1.3a
Control for Reprap
Licensed under the Creative Commons Attributions ShareAlike 3.0 License
Extension Pin Headers
X Stepper
Y Stepper
Z Stepper
Kill Switch / E Stop
A Stepper
Interface
